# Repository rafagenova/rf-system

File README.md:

# radio frequency system for sending and reception of data

## 1. NRF905 notes

### &bull; nrf905 timing to obey info

| nrf905 timing    |   max    |    
| ----------- |   ----------- |
| power down mode to standby mode |   3 ms    |
| standby mode to TX shock burst mode |   650 us    |
| standby mode to RX shock burst mode |   650 us    |
| RX shock burst mode to TX shock burst mode |   550 us    |
| TX shock burst mode to RX shock burst mode |   550 us    |

### &bull; nrf905 modulation
the modulation of nRF905 is Gaussian Frequency Shift Keying (GFSK) with a datarate of 100kbps.
</br> the data is internally Manchester encoded (TX) and Manchester decoded (RX).

### &bull; nrf905 output frequency

Output Frequency
The operating RF-frequency of nRF905 is set in the configuration register by CH_NO and HFREQ_PLL.

| operating frequency|
| ----------- | 
| <i> f = (422.4 + (CH_NO)/10)&bull; (1 + HFREQ_PLL) MHz </i>| 

<i> obs1: CH_NO varies from '000000000' to '1111111111' </i>

<i> obs2: HFREQ_PLL varies from '0' to '1' </i>

| Operating frequency    |   HFREQ_PLL    |    CH_NO   | 
| ----------- |   ----------- | ----------- |
| 430.0 MHz |  [0]   | [001001100]  |
| 433.1 MHz |  [0]   | [001101011]  |
| 433.2 MHz |  [0]   | [001101100]  |
| 434.7 MHz |  [0]   | [001111011]  |
| 862.0 MHz |  [1]   | [001010110]  |
| 868.2 MHz |  [1]   | [001110101]  |
| 868.4 MHz |  [1]   | [001110110]  |
| 869.8 MHz |  [1]   | [001111101]  |
| 902.2 MHz |  [1]   | [100011111]  |
| 902.4 MHz |  [1]   | [100100000]  |
| 927.8 MHz |  [1]   | [110011111]  |

### &bull; nrf905 antenna ports impedance

| optimum differential load impedance at the antenna ports|   frequency    | 
| ----------- | ----------- |
| 225&Omega; + j210 |  900MHz    | 
| 300&Omega; + j100 |  430MHz   | 

<i> obs: a low load impedance (for instance 50&Omega;) can be obtained by fitting a simple matching network or a RF transformer (balun) </i>

### &bull; PCB layout and decoupling guidelines

<i> 

1. A PCB with a minimum of two layers including a ground plane is recommended for optimum performance.

2. The nRF905 DC supply voltage should be decoupled as close as possible to the VDD pins with high performance RF capacitors.

3. It is preferable to mount a large surface mount capacitor (e.g. 4.7uF tantalum) in parallel with the smaller value capacitors.

4. The nRF905 supply voltage should be filtered and routed separately from the supply voltages of any digital circuitry.

5. Long power supply lines on the PCB should be avoided.

6. All device grounds, VDD connections and VDD bypass capacitors must be connected as close as possible to the nRF905 IC.

7. For a PCB with a topside RF ground plane, the VSS pins should be connected directly to the ground plane.

8. For a PCB with a bottom ground plane, the best technique is to place via holes as close as possible to the VSS pins (a minimum of one via hole should be used for each VSS pin).

9. Full swing digital data or control signals should not be routed close to the crystal or the power supply lines.

10. A fully qualified RF-layout for the nRF905 and its surrounding components, including antennas and matching networks, can be downloaded from <b> www.nordicsemi.no. </b>

</i>

| nrf905 features    |   description    |    
| ----------- |   ----------- |
| &bull; Carrier detect |   When the nRF905 is in ShockBurst TM RX, the Carrier Detect (CD) pin is set high if a RF carrier is present at the channel the device is programmed to. </br > </br > This feature is very effective to avoid collision of packages from different transmitters operating at the same frequency. </br > </br > Whenever a device is ready to transmit it could first be set into receive mode and sense whether or not the wanted channel is available for outgoing data.    |
| &bull; Address match |   When the nRF905 is in ShockBurst TM RX mode, the Address Match (AM) pin is set high as soon as an incoming package with an address that is identical with the device’s own identity is received. </br > </br > If Address Match (AM) is high then the MCU can make a decision to wait and see if Data Ready (DR) will be set high indicating a valid data package has been received or ignore that a possible package is being received and switch modes.|
|  &bull; Data ready |   In ShockBurst TM TX Auto Retransmit the Data Ready (DR) signal is set high at the beginning of the pre-amble and is set low at the end of the preamble. The Data Ready (DR) signal therefore pulses at the beginning of each transmitted data packet.  </br > </br > In ShockBurst TM RX, the signal is set high when nRF905 has received a valid package, i.e. a valid address, package length and correct CRC. The MCU can then retrieve the payload via the SPI interface. The Data Ready (DR) pin is reset to low once the data has been clocked out of the data buffer or the device is switched to transmit mode.|
|  &bull; Auto retransmit |   One way to increase system reliability in a noisy environment or in a system without collision control is to transmit a package several times. </br > </br > By setting the AUTO_RETRAN bit to “1” in the configuration register, the circuit keeps sending the same data package as long as TRX_CE and TX_EN is high.|

### &bull; nrf905 schematic example

## 2. Components & schematics

### &bull; voltage regulator (3.7v battery to 3.3v system)

| 3.3V LDO    |   packacge    |    comments |
| ----------- |   ----------- |  ----------- |
| MCP1700T-3302E/TT |  SOT-23-3   |46 in stock at JLCPCB @ 30/05 <br /> Max current of 250 mA <br /> Max dropout voltage of 350 mV |

### &bull; power input schematic

### &bull; transceiver schematic

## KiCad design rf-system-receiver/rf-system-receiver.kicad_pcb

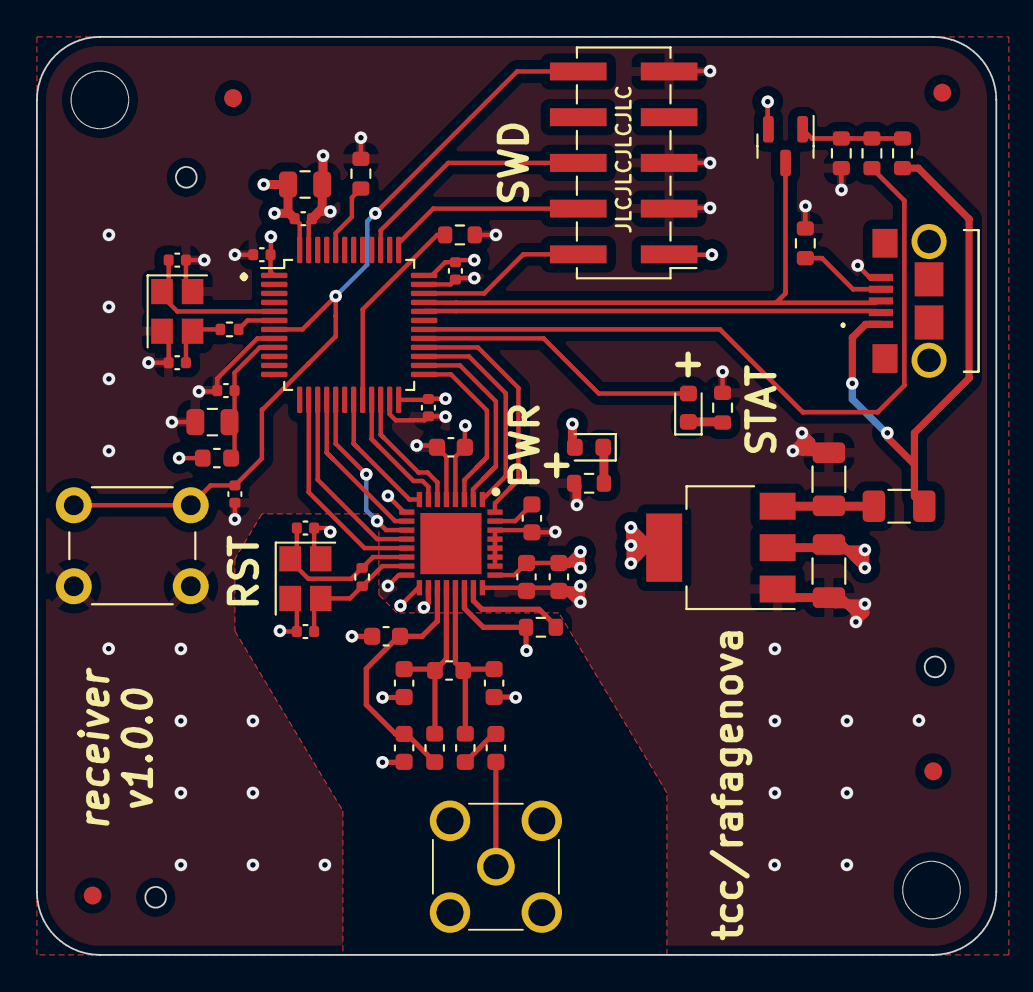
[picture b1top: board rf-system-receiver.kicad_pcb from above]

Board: 4 copper layers, 53.3 x 51.0 mm, 57 parts (0 on the bottom side), 42 nets.

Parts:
C1, C6, C12, C13: 33p/0603; C_0603_1608Metric
C2, C8: 22u/1206; C_1206_3216Metric
C3: 10n/0603; C_0603_1608Metric
C4, C5, C19, C20: 10p/0402; C_0402_1005Metric
C7: 3.3n/0603; C_0603_1608Metric
C9: 4.7n/0603; C_0603_1608Metric
C10, C11: 3.9p/0603; C_0603_1608Metric
C14, C21: 10u/0805; C_0805_2012Metric
C15, C16, C17, C18, C23: 100n/0402; C_0402_1005Metric
C22: 10n/0402; C_0402_1005Metric
D1, D2: RED; LED_0603_1608Metric
F1: ASMD1206-050; Fuse_1206_3216Metric
FB1: 100@100MHz/0603; L_0603_1608Metric
FID1, FID2, FID3, FID4: Fiducial; Fiducial_1mm_Mask2mm
H1, H3: MountingHole; MountingHole_3.2mm_M3
IC1: nRF905; nrf905
J1: USB_B_Micro; 101181930001LF
J2: CONREVSMA001-G; CONREVSMA001G
J3: SWD; PinHeader_2x05_P2.54mm_Vertical_SMD
L1, L2, L3: 12n/0603; L_0603_1608Metric
Q1: MMBT9013; SOT-23
R1: 1M/0402; R_0402_1005Metric
R2: 22k/0603; R_0603_1608Metric
R3, R7: 1k5/0603; R_0603_1608Metric
R4, R6, R9: 10k/0603; R_0603_1608Metric
R5: 47R/0402; R_0402_1005Metric
R8, R11: 100R/0603; R_0603_1608Metric
R10: 36k/0603; R_0603_1608Metric
SW1: SW_Push; SW_PUSH_6mm
U1: STM32F103C8Tx; LQFP-48_7x7mm_P0.5mm
U2: AMS1117-3.3; SOT-223-3_TabPin2
X1, X2: 16MHZ; Crystal_SMD_3225-4Pin_3.2x2.5mm

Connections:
+3.3VA: C21.1, C22.1, FB1.2, U1.9 (VDDA)
+3V3: C1.2, C6.1, C8.1, C9.1, C14.1, C15.1, C16.1, C17.1, C18.1, D1.2 (A), FB1.1, IC1.4 (VDD_1), IC1.17 (VDD_2), IC1.25 (VDD_3), J3.1, Q1.2 (C), U1.1 (VBAT), U1.24 (VDD), U1.36 (VDD), U1.48 (VDD), U2.2 (VO)
+5V: F1.1, J1.1 (VBUS), R9.1
AM: IC1.7 (AM), U1.21 (PB10)
BOOT0: R4.1, U1.44 (BOOT0)
BOOT1: R6.1, U1.20 (PB2)
CD: IC1.6 (CD), U1.22 (PB11)
DR: IC1.8 (DR), U1.19 (PB1)
GND: C1.1, C2.2, C3.1, C4.2, C5.2, C6.2, C7.2, C8.2, C9.2, C10.1, C11.2, C12.2, C14.2, C15.2, C16.2, C17.2, C18.2, C19.2, C20.2, C21.2, C22.2, C23.2, IC1.5 (VSS_1), IC1.9 (VSS_2), IC1.16 (VSS_3), IC1.18 (VSS_4), IC1.22 (VSS_5), IC1.24 (VSS_6), IC1.26 (VSS_7), IC1.27 (VSS_8), IC1.28 (VSS_9), IC1.29 (VSS_10), IC1.30 (VSS_11), J1.5 (GND), J2.2, J2.3, J2.4, J2.5, J3.3, J3.5, J3.9, R2.2, R3.2, R4.2, R6.2, R7.2, R8.2, R10.2, SW1.2, U1.8 (VSSA), U1.23 (VSS), U1.35 (VSS), U1.47 (VSS), U2.1 (GND), X1.2, X1.4, X2.2, X2.4
NRST: C23.1, J3.10, SW1.1, U1.7 (NRST)
unnamed: C2.1, F1.2, U2.3 (VI)
unnamed: C3.2, IC1.31 (DVDD_1V2)
unnamed: C10.2, IC1.21 (ANT2), L1.1, L2.1
unnamed: C11.1, IC1.20 (ANT1), L1.2, L3.2
unnamed: C7.1, C12.1, IC1.19 (VDD_PA), L3.1
unnamed: C13.1, L2.2
unnamed: C13.2, J2.1
unnamed: C20.1, R5.1, X2.3
unnamed: D1.1 (K), R3.1
unnamed: D2.1 (K), R7.1
unnamed: IC1.23 (IREF), R2.1
unnamed: J1.4 (ID), R8.1
unnamed: Q1.1 (B), R9.2, R10.1, R11.1
OSC_IN: C19.1, U1.5 (PD0), X2.1
OSC_OUT: R5.2, U1.6 (PD1)
PWR_UP: IC1.2 (PWR_UP), U1.26 (PB13)
SPI_CSN: IC1.13 (CSN), U1.14 (PA4)
SPI_MISO: IC1.10 (MISO), U1.16 (PA6)
SPI_MOSI: IC1.11 (MOSI), U1.17 (PA7)
SPI_SCK: IC1.12 (SCK), U1.15 (PA5)
STATUS: D2.2 (A), U1.29 (PA8)
SWCLK: J3.4, U1.37 (PA14)
SWDIO: J3.2, U1.34 (PA13)
SWO: J3.6, U1.39 (PB3)
TRX_CE: IC1.1 (TRX_CE), U1.27 (PB14)
TX_EN: IC1.32 (TX_EN), U1.28 (PB15)
UPCLK: IC1.3 (UPCLK), U1.25 (PB12)
USB_D+: J1.3 (D+), Q1.3 (E), U1.33 (PA12)
USB_D-: J1.2 (D-), U1.32 (PA11)
USB_PULLUP: R11.2, U1.30 (PA9)
XC1: C4.1, IC1.14 (XC1), R1.2, X1.1
XC2: C5.1, IC1.15 (XC2), R1.1, X1.3

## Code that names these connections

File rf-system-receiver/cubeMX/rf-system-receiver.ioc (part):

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Mcu.Name=STM32F103C(8-B)Tx
Mcu.Package=LQFP48
Mcu.UserName=STM32F103C8Tx
PA11.Mode=Device
PA11.Signal=USB_DM
PA12.Mode=Device
PA12.Signal=USB_DP
PA13.Mode=Trace_Asynchronous_SW
PA13.Signal=SYS_JTMS-SWDIO
PA14.Mode=Trace_Asynchronous_SW
PA14.Signal=SYS_JTCK-SWCLK
PA4.GPIOParameters=GPIO_Label
PA4.GPIO_Label=SPI1_CSN
PA4.Signal=GPIO_Output
PA5.Mode=Full_Duplex_Master
PA5.Signal=SPI1_SCK
PA6.Mode=Full_Duplex_Master
PA6.Signal=SPI1_MISO
PA7.Mode=Full_Duplex_Master
PA7.Signal=SPI1_MOSI
PB1.GPIOParameters=GPIO_Label
PB1.GPIO_Label=DR
PB1.Signal=GPIO_Output
PB10.GPIOParameters=GPIO_Label
PB10.GPIO_Label=AM
PB10.Signal=GPIO_Output
PB11.GPIOParameters=GPIO_Label
PB11.GPIO_Label=CD
PB11.Signal=GPIO_Output
PB12.GPIOParameters=GPIO_Label
PB12.GPIO_Label=UP_CLK
PB12.Signal=GPIO_Output
PB13.GPIOParameters=GPIO_Label
PB13.GPIO_Label=PWR_UP
PB13.Signal=GPIO_Output
PB14.GPIOParameters=GPIO_Label
PB14.GPIO_Label=TRX_CE
PB14.Signal=GPIO_Output
PB15.GPIOParameters=GPIO_Label
PB15.GPIO_Label=TX_EN
PB15.Signal=GPIO_Output
PB3.Mode=Trace_Asynchronous_SW
PB3.Signal=SYS_JTDO-TRACESWO
PD0-OSC_IN.Mode=HSE-External-Oscillator
PD0-OSC_IN.Signal=RCC_OSC_IN
PD1-OSC_OUT.Mode=HSE-External-Oscillator
PD1-OSC_OUT.Signal=RCC_OSC_OUT
board=custom

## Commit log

2022-08-10 add projects
2022-08-10 add full projects
2022-08-10 deleted transmitter
2022-08-10 add files from transmitter to rf system
2022-08-10 remove cached repo
2022-08-10 add folder
2022-08-10 add files
2022-08-10 add projects to rf-system file
2022-08-10 ibom added
2022-08-11 add silkscreen, fiducials and tooling holes
2022-08-25 adding LCSC Part # and small PCB modifs
